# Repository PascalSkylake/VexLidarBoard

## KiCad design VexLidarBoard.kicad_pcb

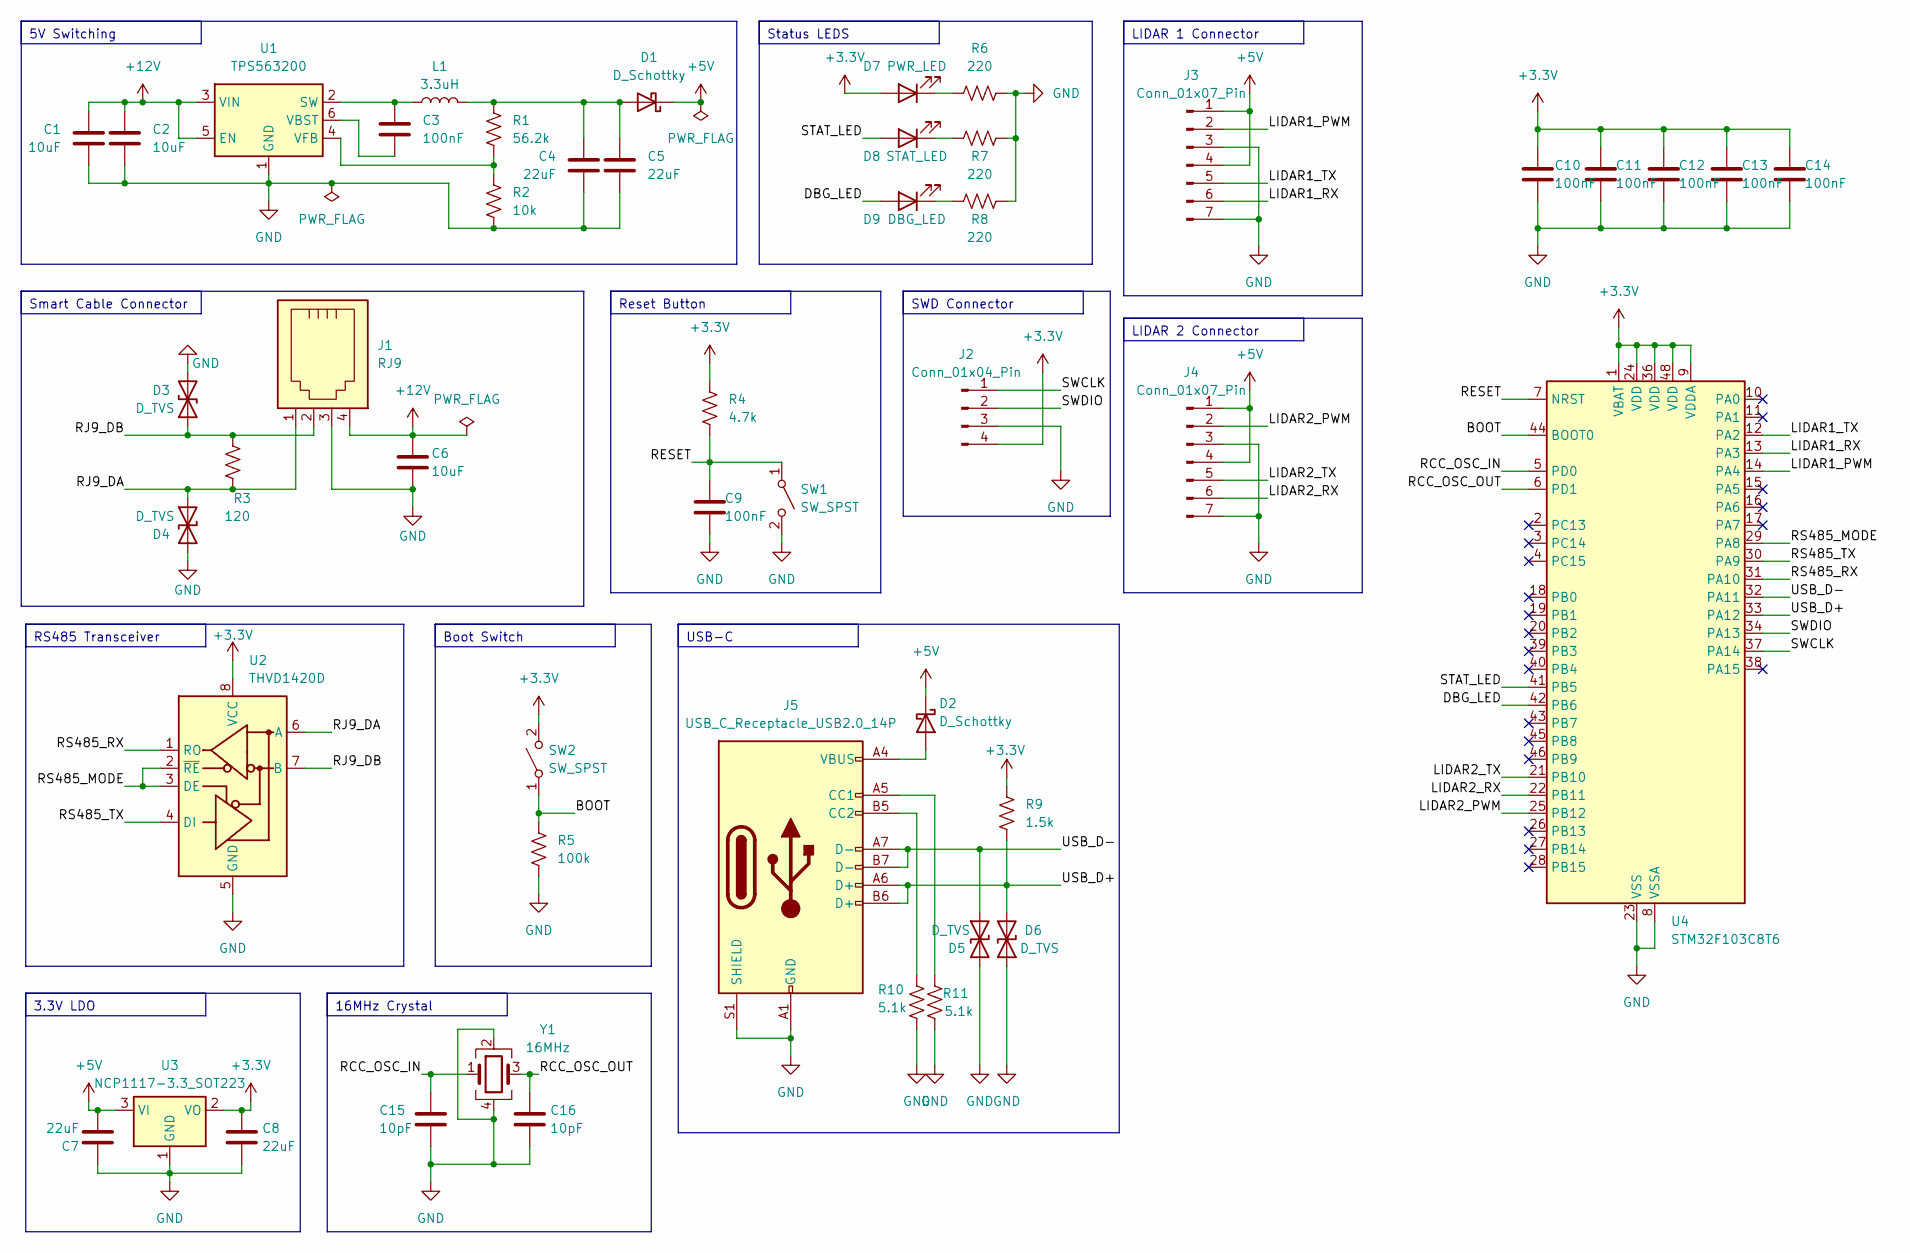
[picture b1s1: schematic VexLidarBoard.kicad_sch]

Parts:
C1, C2, C6: 10uF; C_0805_2012Metric_Pad1.18x1.45mm_HandSolder
C3, C9, C10, C11, C12, C13, C14: 100nF; C_0805_2012Metric_Pad1.18x1.45mm_HandSolder
C4, C5, C7, C8: 22uF; C_0805_2012Metric_Pad1.18x1.45mm_HandSolder
C15, C16: 10pF; C_0805_2012Metric_Pad1.18x1.45mm_HandSolder
D1, D2: D_Schottky; D_0805_2012Metric_Pad1.15x1.40mm_HandSolder
D3, D4, D5, D6: D_TVS; D_1206_3216Metric_Pad1.42x1.75mm_HandSolder
D7: PWR_LED; LED_0805_2012Metric_Pad1.15x1.40mm_HandSolder
D8: STAT_LED; LED_0805_2012Metric_Pad1.15x1.40mm_HandSolder
D9: DBG_LED; LED_0805_2012Metric_Pad1.15x1.40mm_HandSolder
J1: RJ9; RJ9_Evercom_5301-440xxx_Horizontal
J2: Conn_01x04_Pin; PinSocket_1x04_P2.54mm_Vertical
J3, J4: Conn_01x07_Pin; Molex_PicoBlade_53261-0771_1x07-1MP_P1.25mm_Horizontal
J5: USB_C_Receptacle_USB2.0_14P; USB_C_Receptacle_GCT_USB4105-xx-A_16P_TopMnt_Horizontal
L1: 3.3uH; L_Abracon_ASPI-0425
R1: 56.2k; R_0805_2012Metric_Pad1.20x1.40mm_HandSolder
R2: 10k; R_0805_2012Metric_Pad1.20x1.40mm_HandSolder
R3: 120; R_0805_2012Metric_Pad1.20x1.40mm_HandSolder
R4: 4.7k; R_0805_2012Metric_Pad1.20x1.40mm_HandSolder
R5: 100k; R_0805_2012Metric_Pad1.20x1.40mm_HandSolder
R6, R7, R8: 220; R_0805_2012Metric_Pad1.20x1.40mm_HandSolder
R9: 1.5k; R_0805_2012Metric_Pad1.20x1.40mm_HandSolder
R10, R11: 5.1k; R_0805_2012Metric_Pad1.20x1.40mm_HandSolder
SW1, SW2: SW_SPST; SW_Tactile_SPST_NO_Straight_CK_PTS636Sx25SMTRLFS
U1: TPS563200; SOT-23-6
U2: THVD1420D; SOIC-8_3.9x4.9mm_P1.27mm
U3: NCP1117-3.3_SOT223; SOT-223-3_TabPin2
U4: STM32F103C8T6; LQFP-48_7x7mm_P0.5mm
Y1: 16MHz; Crystal_SMD_3225-4Pin_3.2x2.5mm_HandSoldering

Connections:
+3.3V: C8.1, C10.1, C11.1, C12.1, C13.1, C14.1, D7.2 (A), J2.4, R4.1, R9.1, SW2.2 (B), U2.8 (VCC), U3.2 (VO), U4.1 (VBAT), U4.9 (VDDA), U4.24 (VDD), U4.36 (VDD), U4.48 (VDD)
+5V: C7.2, D1.1 (K), D2.1 (K), J3.1, J3.4, J4.1, J4.4, U3.3 (VI)
+12V: C1.1, C2.1, C6.1, J1.4, U1.3 (VIN), U1.5 (EN)
/BOOT: R5.1, SW2.1 (A), U4.44 (BOOT0)
/DBG_LED: D9.2 (A), U4.42 (PB6)
/LIDAR1_PWM: J3.2, U4.14 (PA4)
/LIDAR1_RX: J3.6, U4.13 (PA3)
/LIDAR1_TX: J3.5, U4.12 (PA2)
/LIDAR2_PWM: J4.2, U4.25 (PB12)
/LIDAR2_RX: J4.6, U4.22 (PB11)
/LIDAR2_TX: J4.5, U4.21 (PB10)
/RCC_OSC_IN: C15.1, U4.5 (PD0), Y1.1
/RCC_OSC_OUT: C16.1, U4.6 (PD1), Y1.3
/RESET: C9.1, R4.2, SW1.1 (A), U4.7 (NRST)
/RJ9_DA: D4.1 (A1), J1.1, R3.2, U2.6 (A)
/RJ9_DB: D3.1 (A1), J1.2, R3.1, U2.7 (B)
/RS485_MODE: U2.2 (~RE), U2.3 (DE), U4.29 (PA8)
/RS485_RX: U2.1 (RO), U4.31 (PA10)
/RS485_TX: U2.4 (DI), U4.30 (PA9)
/STAT_LED: D8.2 (A), U4.41 (PB5)
/SWCLK: J2.1, U4.37 (PA14)
/SWDIO: J2.2, U4.34 (PA13)
/USB_D+: D6.2 (A2), J5.A6 (D+), J5.B6 (D+), R9.2, U4.33 (PA12)
/USB_D-: D5.1 (A1), J5.A7 (D-), J5.B7 (D-), U4.32 (PA11)
GND: C1.2, C2.2, C4.2, C5.2, C6.2, C7.1, C8.2, C9.2, C10.2, C11.2, C12.2, C13.2, C14.2, C15.2, C16.2, D3.2 (A2), D4.2 (A2), D5.2 (A2), D6.1 (A1), J1.3, J2.3, J3.3, J3.7, J3.MP, J4.3, J4.7, J4.MP, J5.A1 (GND), J5.A12 (GND), J5.B1 (GND), J5.B12 (GND), J5.S1 (SHIELD), R2.2, R5.2, R6.2, R7.2, R8.2, R10.2, R11.2, SW1.2 (B), U1.1 (GND), U2.5 (GND), U3.1 (GND), U4.8 (VSSA), U4.23 (VSS), U4.35 (VSS), U4.47 (VSS), Y1.2, Y1.4
unnamed: C4.1, C5.1, D1.2 (A), L1.2, R1.1
unnamed: D2.2 (A), J5.A4 (VBUS), J5.A9 (VBUS), J5.B4 (VBUS), J5.B9 (VBUS)
unnamed: D7.1 (K), R6.1
unnamed: D8.1 (K), R7.1
unnamed: D9.1 (K), R8.1
unnamed: J5.A5 (CC1), R11.1
unnamed: J5.B5 (CC2), R10.1
unnamed: C3.1, L1.1, U1.2 (SW)
unnamed: C3.2, U1.6 (VBST)
unnamed: R1.2, R2.1, U1.4 (VFB)

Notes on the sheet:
16MHz Crystal
5V Switching
RS485 Transceiver
Boot Switch
USB-C
LIDAR 1 Connector
SWD Connector
Reset Button
3.3V LDO
Smart Cable Connector
LIDAR 2 Connector
Status LEDS

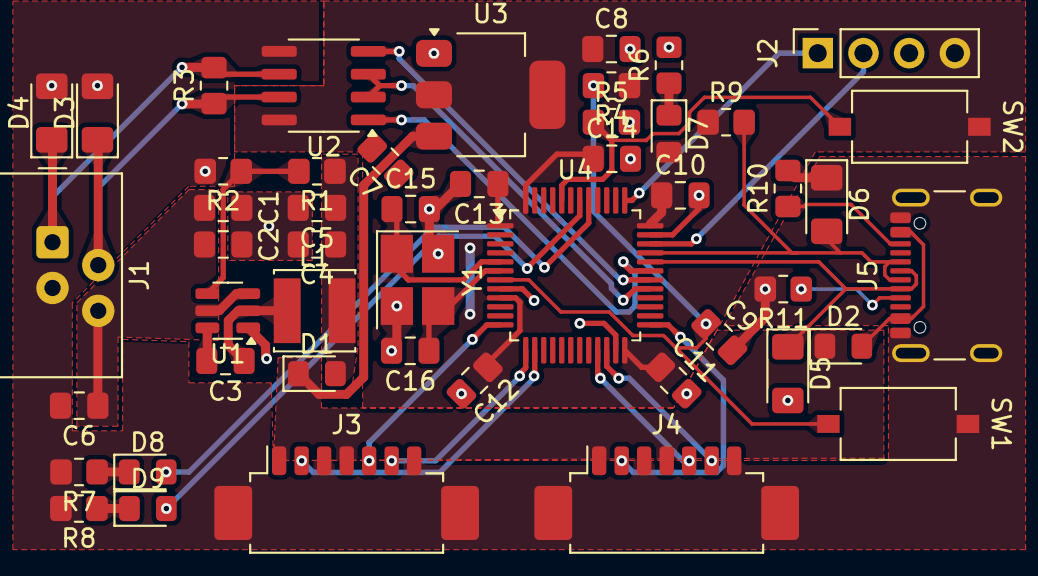
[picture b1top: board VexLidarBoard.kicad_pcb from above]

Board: 2 copper layers, 49 parts (0 on the bottom side), 35 nets.

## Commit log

2025-09-17 add to git
2025-09-18 routing almost done
2025-09-18 done for real
2025-09-18 done layout
